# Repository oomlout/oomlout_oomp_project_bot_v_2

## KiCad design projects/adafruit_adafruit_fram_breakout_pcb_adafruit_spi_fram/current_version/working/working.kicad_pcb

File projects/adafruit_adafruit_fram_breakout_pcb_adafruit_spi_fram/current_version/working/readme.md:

# adafruit_fram_breakout_pcb
 
## summary 
* id: adafruit_adafruit_fram_breakout_pcb_adafruit_spi_fram
* user: adafruit
* name: adafruit_fram_breakout_pcb
* board: adafruit_spi_fram
* repo: https://github.com/adafruit/Adafruit-FRAM-Breakout-PCB

* src_file_repo_sch: 
* src_file_repo_sch_link: https://github.com/adafruit/Adafruit-FRAM-Breakout-PCB/tree/master/
* full details link: https://github.com/oomlout/oomlout_oomp_project_bot_v_2/tree/main/projects/adafruit_adafruit_fram_breakout_pcb_adafruit_spi_fram/current_version/working  

## schematic  
  
[schematic (pdf)](working_schematic.pdf) 

## pcb  

[board (pdf)](working.pdf)  

## working_bom
| Id | Designator | Footprint | Quantity | Designation | Supplier and ref |  | None | 
| --- | --- | --- | --- | --- | --- | --- | --- | 
| 1 | FID2,FID1 | FIDUCIAL_1MM | 2 | FIDUCIAL" |  |  | [''] | 
| 2 | U$5,U$6 | MOUNTINGHOLE_2.5_PLATED | 2 | MOUNTINGHOLE2.5 |  |  | [''] | 
| 3 | C1 | _0805MP | 1 | 10uF |  |  | [''] | 
| 4 | JP1 | 1X08_ROUND_70 | 1 |  |  |  | [''] | 
| 5 | R2,R1 | _0805MP | 2 | 10K |  |  | [''] | 
| 6 | U$4 | ADAFRUIT_3.5MM | 1 |  |  |  | [''] | 
| 7 | U1 | SOIC8_208MIL | 1 | MB85RC256VPF-G-JNERE2 |  |  | [''] | 

## bom_schematic
| Ref | Qnty | Value | Cmp name | Footprint | Description | Vendor | DNP | 
| --- | --- | --- | --- | --- | --- | --- | --- | 
| C1 | 1 | 10uF | CAP_CERAMIC_0805MP | working:_0805MP |  |  |  | 
| FID1, FID2 | 2 | FIDUCIAL"" | FIDUCIAL{dblquote}{dblquote} | working:FIDUCIAL_1MM |  |  |  | 
| JP1 | 1 | HEADER-1X870MIL | HEADER-1X870MIL | working:1X08_ROUND_70 |  |  |  | 
| R1, R2 | 2 | 10K | RESISTOR_0805MP | working:_0805MP |  |  |  | 
| U1 | 1 | MB85RC256VPF-G-JNERE2 | FRAM_SOIC8_I2C | working:SOIC8_208MIL |  |  |  | 
| U$5, U$6 | 2 | MOUNTINGHOLE2.5 | MOUNTINGHOLE2.5 | working:MOUNTINGHOLE_2.5_PLATED |  |  |  | 

## mounting_holes
| x | y | package | value | ref | size | 
| --- | --- | --- | --- | --- | --- | 
| 0.0 | 0.0 | MOUNTINGHOLE_2.5_PLATED | MOUNTINGHOLE2.5 | U$5 | m3 | 
| 15.24 | 0.0 | MOUNTINGHOLE_2.5_PLATED | MOUNTINGHOLE2.5 | U$6 | m3 |

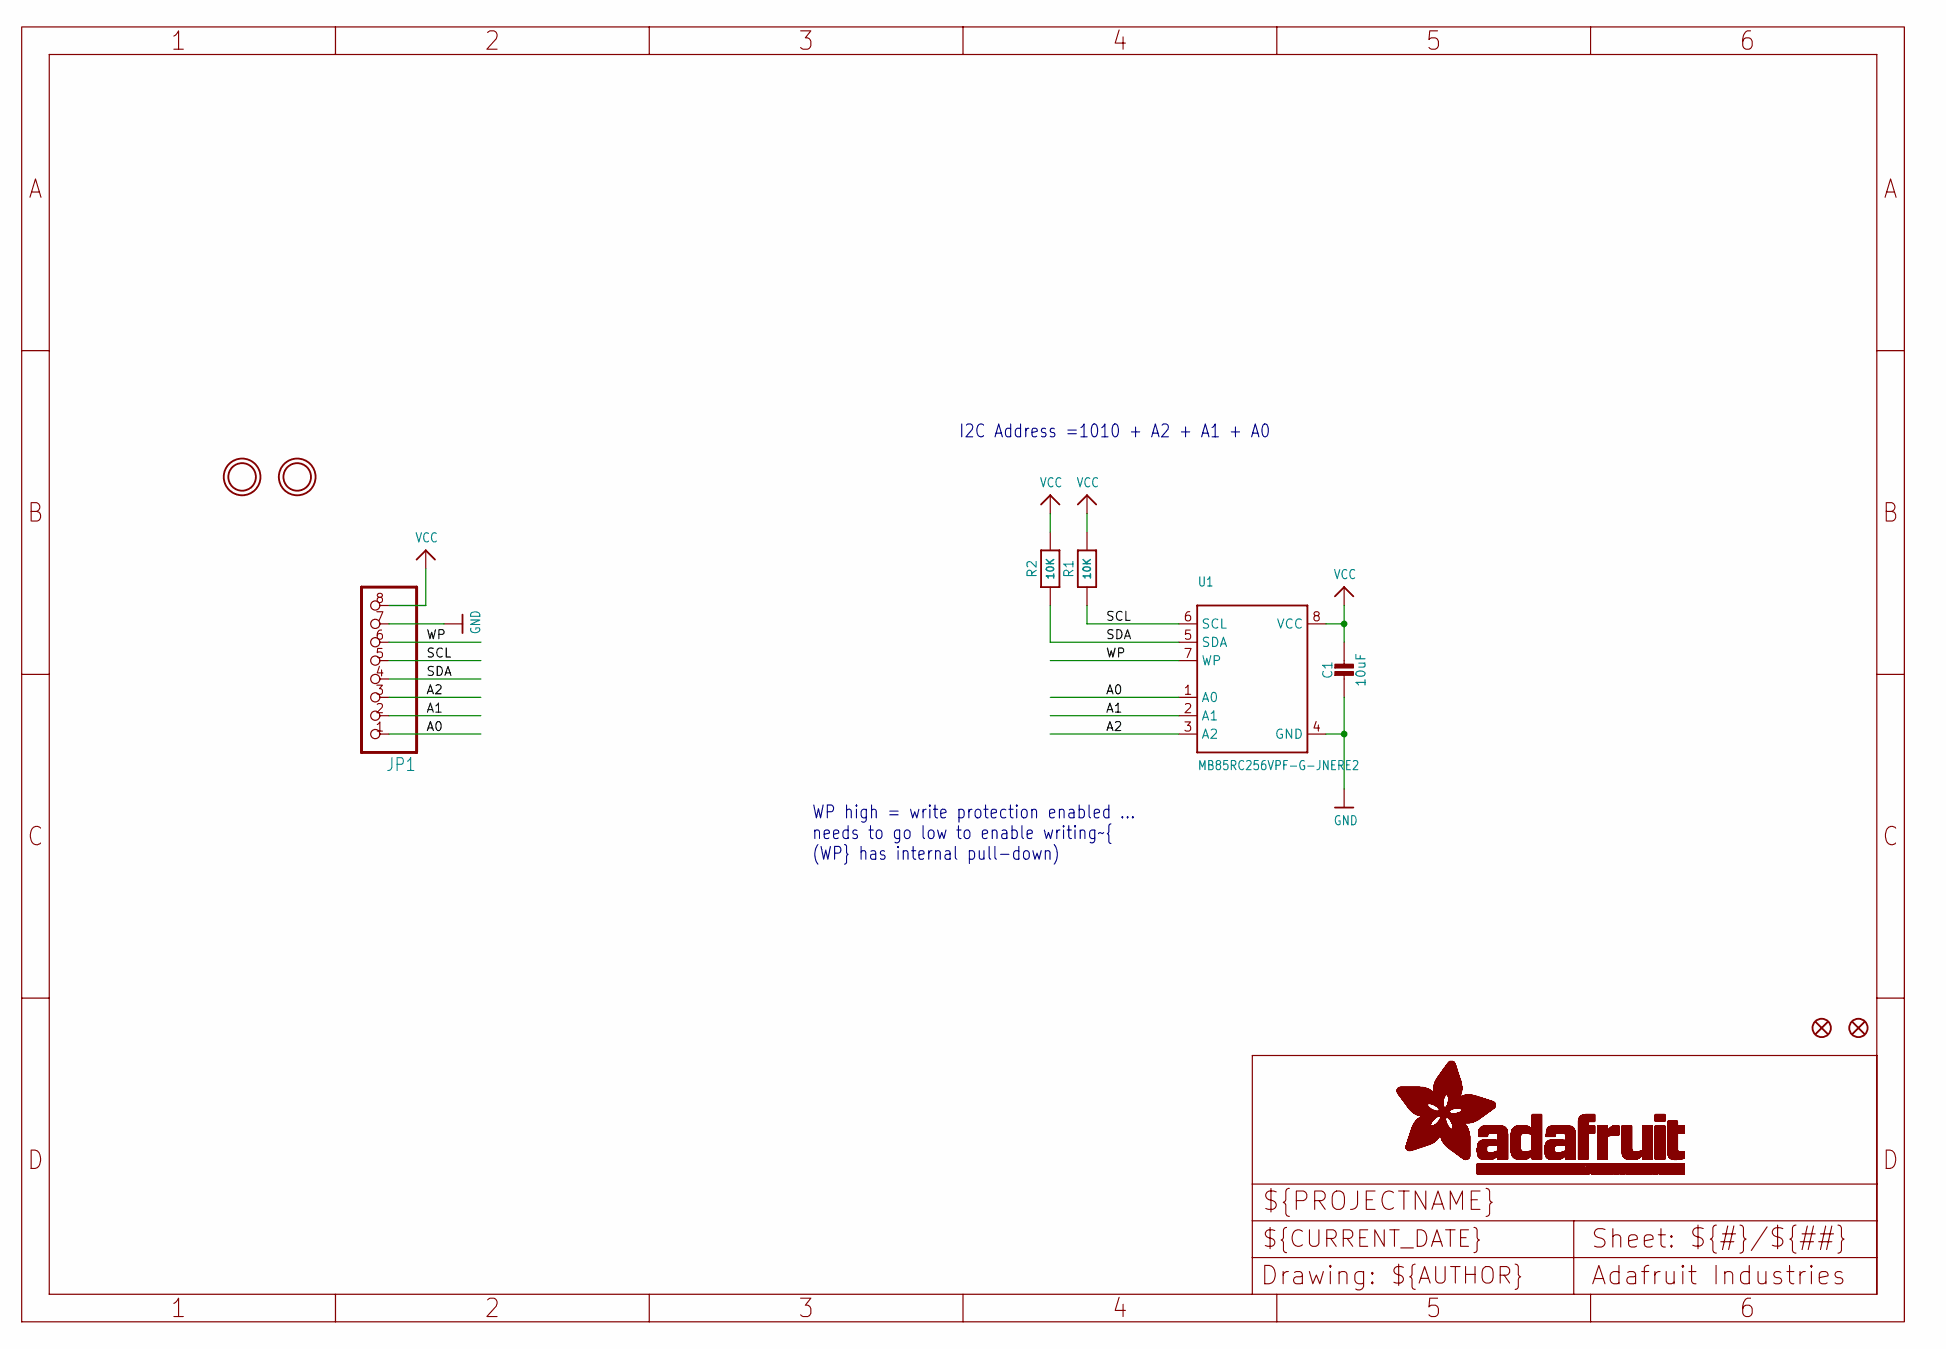
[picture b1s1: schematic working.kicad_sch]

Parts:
C1: 10uF; _0805MP
FID1, FID2: FIDUCIAL""; FIDUCIAL_1MM
JP1: HEADER-1X870MIL; 1X08_ROUND_70
R1, R2: 10K; _0805MP
U1: MB85RC256VPF-G-JNERE2; SOIC8_208MIL
U$5, U$6: MOUNTINGHOLE2.5; MOUNTINGHOLE_2.5_PLATED

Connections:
A0: JP1.1, U1.1 (A0)
A1: JP1.2, U1.2 (A1)
A2: JP1.3, U1.3 (A2)
GND: C1.2, JP1.7, U1.4 (GND)
SCL: JP1.5, R1.1, U1.6 (SCL)
SDA: JP1.4, R2.1, U1.5 (SDA)
VCC: C1.1, JP1.8, R1.2, R2.2, U1.8 (VCC)
WP: JP1.6, U1.7 (WP)

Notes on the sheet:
I2C Address =1010 + A2 + A1 + A0
WP high = write protection enabled ... needs to go low to enable writing~{ (WP} has internal pull-down)

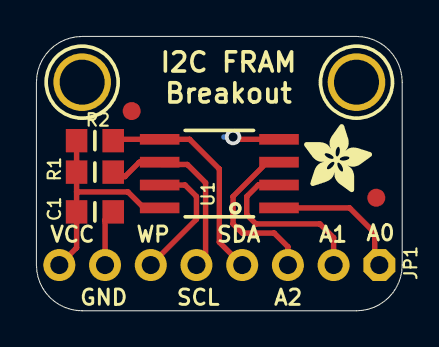
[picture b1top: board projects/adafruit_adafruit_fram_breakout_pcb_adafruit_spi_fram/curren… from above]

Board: 2 copper layers, 20.3 x 15.2 mm, 10 parts (0 on the bottom side), 8 nets.

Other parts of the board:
U$4: ADAFRUIT_3.5MM

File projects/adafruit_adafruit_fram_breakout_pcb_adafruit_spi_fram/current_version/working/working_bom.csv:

"Id";"Designator";"Footprint";"Quantity";"Designation";"Supplier and ref";
1;"FID2,FID1";"FIDUCIAL_1MM";2;"FIDUCIAL""";;;
2;"U$5,U$6";"MOUNTINGHOLE_2.5_PLATED";2;"MOUNTINGHOLE2.5";;;
3;"C1";"_0805MP";1;"10uF";;;
4;"JP1";"1X08_ROUND_70";1;"";;;
5;"R2,R1";"_0805MP";2;"10K";;;
6;"U$4";"ADAFRUIT_3.5MM";1;"";;;
7;"U1";"SOIC8_208MIL";1;"MB85RC256VPF-G-JNERE2";;;

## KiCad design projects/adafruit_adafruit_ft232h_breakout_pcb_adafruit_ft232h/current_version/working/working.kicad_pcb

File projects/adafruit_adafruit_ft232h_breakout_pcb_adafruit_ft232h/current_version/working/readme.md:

# adafruit_ft232h_breakout_pcb
 
## summary 
* id: adafruit_adafruit_ft232h_breakout_pcb_adafruit_ft232h
* user: adafruit
* name: adafruit_ft232h_breakout_pcb
* board: adafruit_ft232h
* repo: https://github.com/adafruit/Adafruit-FT232H-Breakout-PCB

* src_file_repo_sch: 
* src_file_repo_sch_link: https://github.com/adafruit/Adafruit-FT232H-Breakout-PCB/tree/master/
* full details link: https://github.com/oomlout/oomlout_oomp_project_bot_v_2/tree/main/projects/adafruit_adafruit_ft232h_breakout_pcb_adafruit_ft232h/current_version/working  

## schematic  
  
[schematic (pdf)](working_schematic.pdf) 

## pcb  

[board (pdf)](working.pdf)  

## working_bom
| Id | Designator | Footprint | Quantity | Designation | Supplier and ref |  | None | 
| --- | --- | --- | --- | --- | --- | --- | --- | 
| 1 | R2 | 0805-NO | 1 | 12K 1% |  |  | [''] | 
| 2 | R4,R3 | 0805-NO | 2 | 1K |  |  | [''] | 
| 3 | LED1 | CHIPLED_0805_NOOUTLINE | 1 | green |  |  | [''] | 
| 4 | U$8 | ADAFRUIT_5MM | 1 |  |  |  | [''] | 
| 5 | U$11 | PCBFEAT-REV-040 | 1 |  |  |  | [''] | 
| 6 | X1 | 4UCONN_20329 | 1 | MiniB |  |  | [''] | 
| 7 | U$6,U$4,U$7,U$5 | MOUNTINGHOLE_2.5_PLATED | 4 | MOUNTINGHOLE2.5 |  |  | [''] | 
| 8 | IC1 | SOT23-6 | 1 | 93LC56B |  |  | [''] | 
| 9 | C8,C7,C6,C2 | 0805-NO | 4 | 0.1uF |  |  | [''] | 
| 10 | FID1,FID2 | FIDUCIAL_1MM | 2 | FIDUCIAL" |  |  | [''] | 
| 11 | FB2,FB1 | _0805 | 2 | Ferrite |  |  | [''] | 
| 12 | R5 | _0805MP | 1 | 2.2K |  |  | [''] | 
| 13 | C4,C1,C3,C5 | 0805-NO | 4 | 10uF |  |  | [''] | 
| 14 | R6 | 0805-NO | 1 | 4.7K |  |  | [''] | 
| 15 | IC2 | QFN48_8MM | 1 | FT232HQ |  |  | [''] | 
| 16 | LED2 | CHIPLED_0805_NOOUTLINE | 1 | red |  |  | [''] | 
| 17 | R7,R1 | 0805-NO | 2 | 12K |  |  | [''] | 
| 18 | U$2,U$3 | 1X10-BIG | 2 | PINHD-1X10 |  |  | [''] | 
| 19 | Q1 | RESONATOR-SMD | 1 | CSTCR 12MHz |  |  | [''] | 
| 20 | U$9 | ADAFRUIT_TEXT_30MM | 1 |  |  |  | [''] | 

## bom_schematic
| Ref | Qnty | Value | Cmp name | Footprint | Description | Vendor | DNP | 
| --- | --- | --- | --- | --- | --- | --- | --- | 
| C1, C3, C4, C5 | 4 | 10uF | CAP_CERAMIC0805-NOOUTLINE | working:0805-NO |  |  |  | 
| C2, C6, C7, C8 | 4 | 0.1uF | CAP_CERAMIC0805-NOOUTLINE | working:0805-NO |  |  |  | 
| FB1, FB2 | 2 | Ferrite | FERRITE_0805 | working:_0805 |  |  |  | 
| FID1, FID2 | 2 | FIDUCIAL"" | FIDUCIAL{dblquote}{dblquote} | working:FIDUCIAL_1MM |  |  |  | 
| IC1 | 1 | 9376?A | 9376?A | working:SOT23-6 |  |  |  | 
| IC2 | 1 | FT232HQ | FT232HQ | working:QFN48_8MM |  |  |  | 
| LED1 | 1 | green | LED0805_NOOUTLINE | working:CHIPLED_0805_NOOUTLINE |  |  |  | 
| LED2 | 1 | red | LED0805_NOOUTLINE | working:CHIPLED_0805_NOOUTLINE |  |  |  | 
| Q1 | 1 | RESONATORSMD | RESONATORSMD | working:RESONATOR-SMD |  |  |  | 
| R1, R7 | 2 | 12K | RESISTOR0805_NOOUTLINE | working:0805-NO |  |  |  | 
| R2 | 1 | 12K 1% | RESISTOR0805_NOOUTLINE | working:0805-NO |  |  |  | 
| R3, R4 | 2 | 1K | RESISTOR0805_NOOUTLINE | working:0805-NO |  |  |  | 
| R5 | 1 | 2.2K | RESISTOR_0805MP | working:_0805MP |  |  |  | 
| R6 | 1 | 4.7K | RESISTOR0805_NOOUTLINE | working:0805-NO |  |  |  | 
| U$2, U$3 | 2 | PINHD-1X10 | PINHD-1X10 | working:1X10-BIG |  |  |  | 
| U$4, U$5, U$6, U$7 | 4 | MOUNTINGHOLE2.5 | MOUNTINGHOLE2.5 | working:MOUNTINGHOLE_2.5_PLATED |  |  |  | 
| X1 | 1 | MiniB | USBMICRO_20329 | working:4UCONN_20329 |  |  |  | 

## mounting_holes
| x | y | package | value | ref | size | 
| --- | --- | --- | --- | --- | --- | 
| 0.0 | 17.78 | MOUNTINGHOLE_2.5_PLATED | MOUNTINGHOLE2.5 | U$4 | m3 | 
| 0.0 | 0.0 | MOUNTINGHOLE_2.5_PLATED | MOUNTINGHOLE2.5 | U$5 | m3 | 
| 33.02 | 17.78 | MOUNTINGHOLE_2.5_PLATED | MOUNTINGHOLE2.5 | U$6 | m3 | 
| 33.02 | 0.0 | MOUNTINGHOLE_2.5_PLATED | MOUNTINGHOLE2.5 | U$7 | m3 |

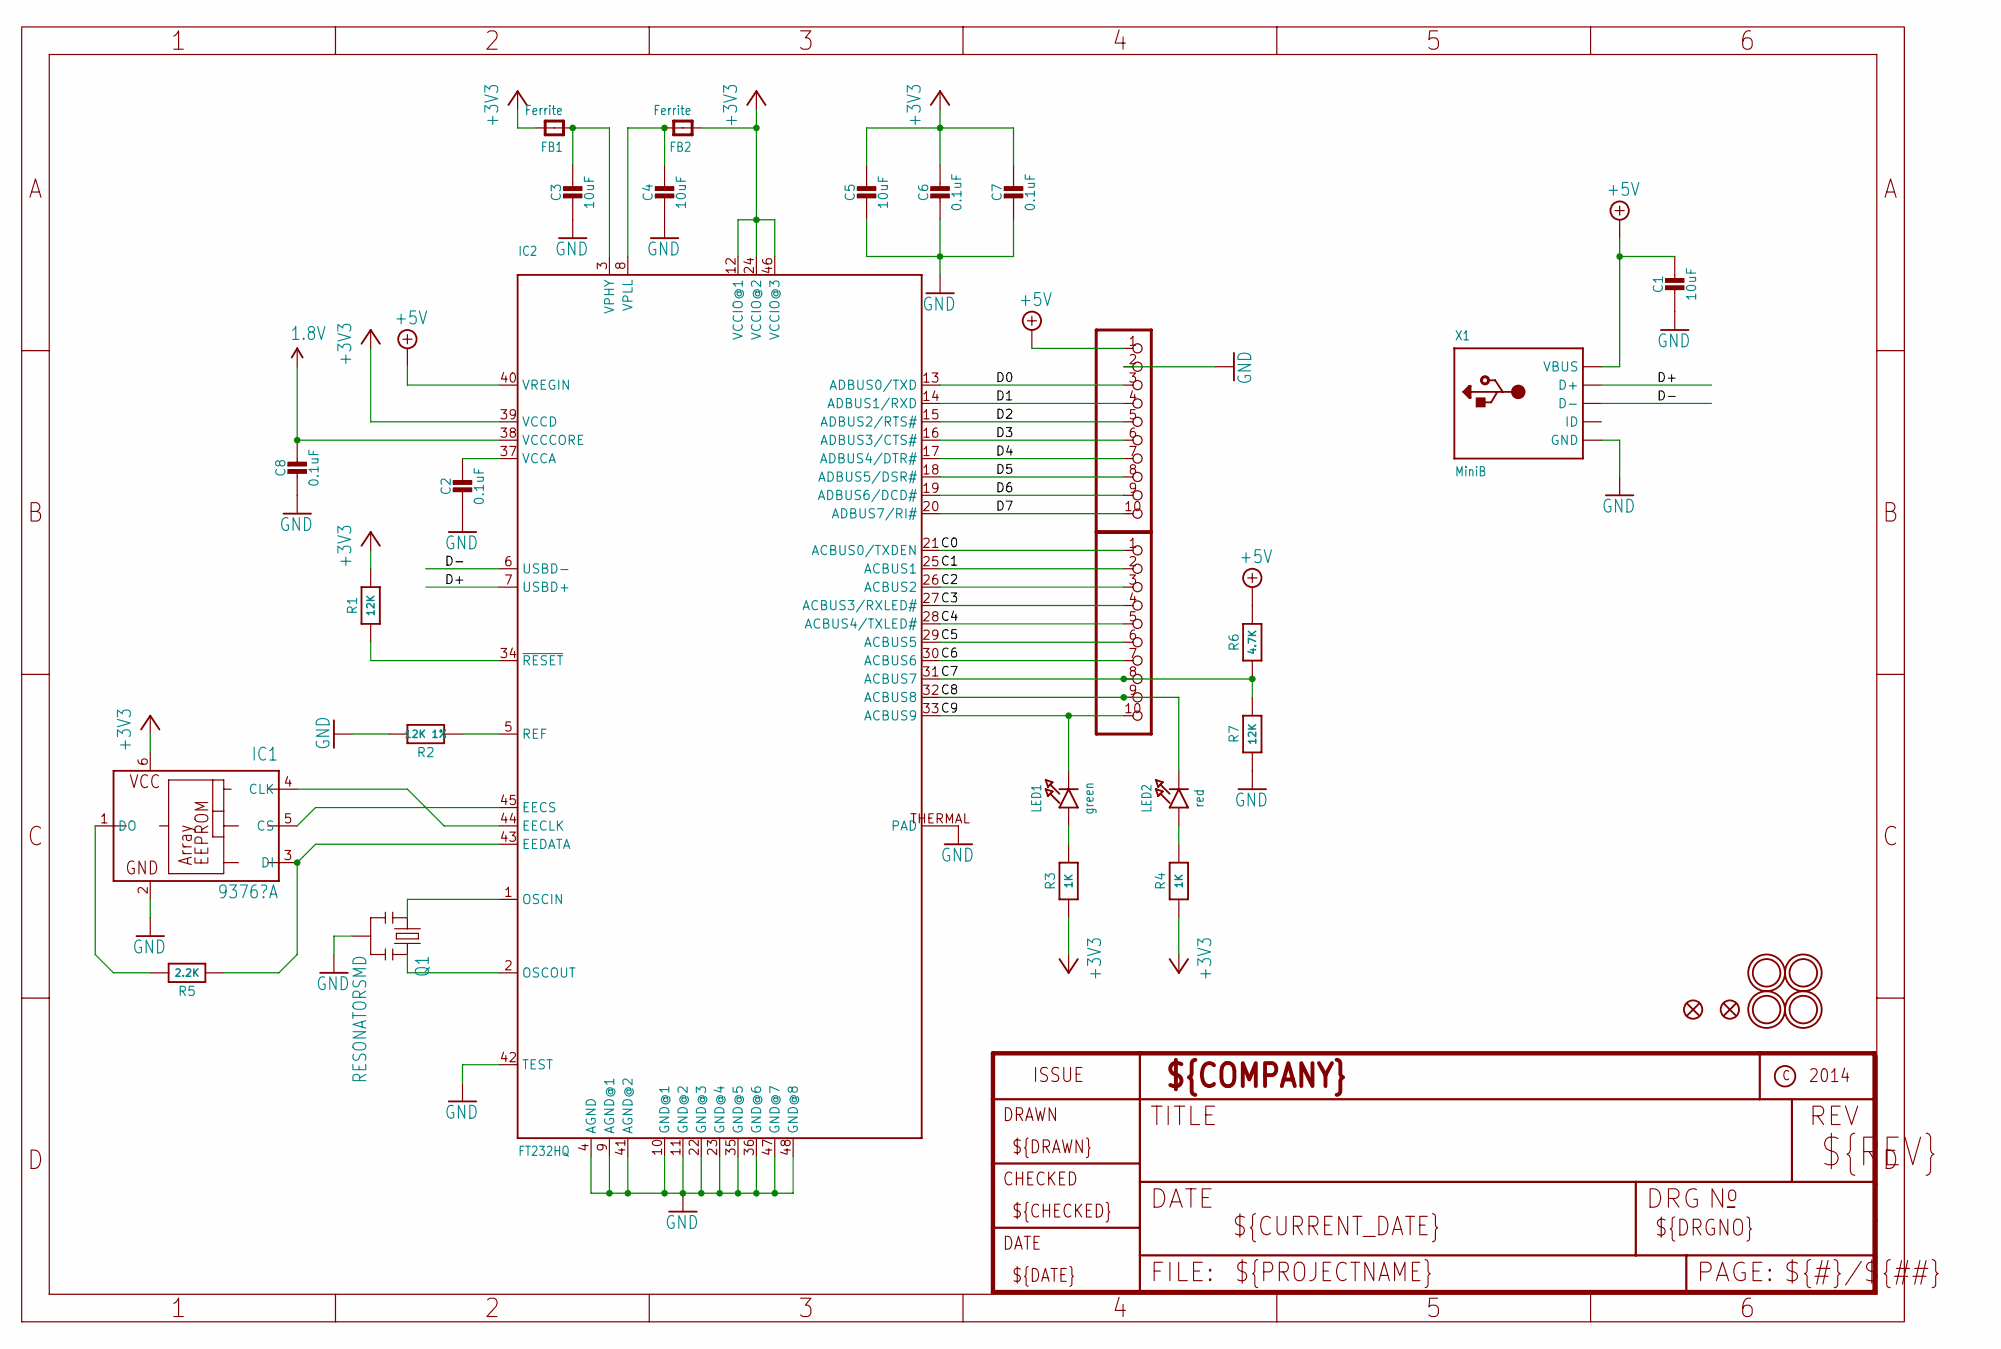
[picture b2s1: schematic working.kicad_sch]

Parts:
C1, C3, C4, C5: 10uF; 0805-NO
C2, C6, C7, C8: 0.1uF; 0805-NO
FB1, FB2: Ferrite; _0805
FID1, FID2: FIDUCIAL""; FIDUCIAL_1MM
IC1: 9376?A; SOT23-6
IC2: FT232HQ; QFN48_8MM
LED1: green; CHIPLED_0805_NOOUTLINE
LED2: red; CHIPLED_0805_NOOUTLINE
Q1: RESONATORSMD; RESONATOR-SMD
R1, R7: 12K; 0805-NO
R2: 12K 1%; 0805-NO
R3, R4: 1K; 0805-NO
R5: 2.2K; _0805MP
R6: 4.7K; 0805-NO
U$2, U$3: PINHD-1X10; 1X10-BIG
U$4, U$5, U$6, U$7: MOUNTINGHOLE2.5; MOUNTINGHOLE_2.5_PLATED
X1: MiniB; 4UCONN_20329

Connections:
1.8V: C8.1, IC2.38 (VCCCORE)
+3V3: C5.1, C6.1, C7.1, FB1.2, FB2.1, IC1.6 (VCC), IC2.12 (VCCIO@1), IC2.24 (VCCIO@2), IC2.39 (VCCD), IC2.46 (VCCIO@3), R1.2, R3.1, R4.1
+5V: C1.1, IC2.40 (VREGIN), R6.2, U$2.1, X1.VBUS
C0: IC2.21 (ACBUS0/TXDEN), U$3.1
C1: IC2.25 (ACBUS1), U$3.2
C2: IC2.26 (ACBUS2), U$3.3
C3: IC2.27 (ACBUS3/RXLED#), U$3.4
C4: IC2.28 (ACBUS4/TXLED#), U$3.5
C5: IC2.29 (ACBUS5), U$3.6
C6: IC2.30 (ACBUS6), U$3.7
C7: IC2.31 (ACBUS7), R6.1, R7.2, U$3.8
C8: IC2.32 (ACBUS8), LED2.C, U$3.9
C9: IC2.33 (ACBUS9), LED1.C, U$3.10
D0: IC2.13 (ADBUS0/TXD), U$2.3
D1: IC2.14 (ADBUS1/RXD), U$2.4
D2: IC2.15 (ADBUS2/RTS#), U$2.5
D3: IC2.16 (ADBUS3/CTS#), U$2.6
D4: IC2.17 (ADBUS4/DTR#), U$2.7
D5: IC2.18 (ADBUS5/DSR#), U$2.8
D6: IC2.19 (ADBUS6/DCD#), U$2.9
D7: IC2.20 (ADBUS7/RI#), U$2.10
D+: IC2.7 (USBD+), X1.D+
D-: IC2.6 (USBD-), X1.D-
GND: C1.2, C2.2, C3.2, C4.2, C5.2, C6.2, C7.2, C8.2, IC1.2 (GND), IC2.4 (AGND), IC2.9 (AGND@1), IC2.10 (GND@1), IC2.11 (GND@2), IC2.22 (GND@3), IC2.23 (GND@4), IC2.35 (GND@5), IC2.36 (GND@6), IC2.41 (AGND@2), IC2.42 (TEST), IC2.47 (GND@7), IC2.48 (GND@8), IC2.THERMAL (PAD), Q1.2, R2.2, R7.1, U$2.2, X1.BASE@1 (GND), X1.BASE@2 (GND), X1.GND, X1.SPRT@1 (GND), X1.SPRT@2 (GND), X1.SPRT@3 (GND), X1.SPRT@4 (GND)
unnamed: IC2.1 (OSCIN), Q1.1
unnamed: IC2.2 (OSCOUT), Q1.3
unnamed: IC2.5 (REF), R2.1
unnamed: LED2.A, R4.2
unnamed: IC2.34 (~RESET), R1.1
unnamed: LED1.A, R3.2
unnamed: IC1.3 (DI), IC2.43 (EEDATA), R5.1
unnamed: IC1.5 (CS), IC2.45 (EECS)
unnamed: IC1.4 (CLK), IC2.44 (EECLK)
unnamed: IC1.1 (DO), R5.2
VCCA: C2.1, IC2.37 (VCCA)
VPHY: C3.1, FB1.1, IC2.3 (VPHY)
VPLL: C4.1, FB2.2, IC2.8 (VPLL)

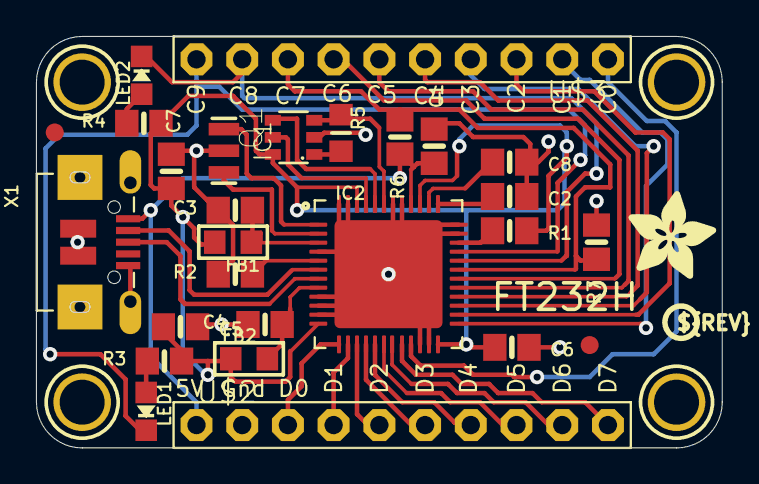
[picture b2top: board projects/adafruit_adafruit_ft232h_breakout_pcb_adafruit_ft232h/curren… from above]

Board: 2 copper layers, 38.1 x 22.9 mm, 34 parts (1 on the bottom side), 37 nets.

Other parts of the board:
U$8: ADAFRUIT_5MM
U$9: ADAFRUIT_TEXT_30MM
U$11: PCBFEAT-REV-040

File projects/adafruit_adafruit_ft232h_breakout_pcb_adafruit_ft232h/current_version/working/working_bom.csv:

"Id";"Designator";"Footprint";"Quantity";"Designation";"Supplier and ref";
1;"R2";"0805-NO";1;"12K 1%";;;
2;"R4,R3";"0805-NO";2;"1K";;;
3;"LED1";"CHIPLED_0805_NOOUTLINE";1;"green";;;
4;"U$8";"ADAFRUIT_5MM";1;"";;;
5;"U$11";"PCBFEAT-REV-040";1;"";;;
6;"X1";"4UCONN_20329";1;"MiniB";;;
7;"U$6,U$4,U$7,U$5";"MOUNTINGHOLE_2.5_PLATED";4;"MOUNTINGHOLE2.5";;;
8;"IC1";"SOT23-6";1;"93LC56B";;;
9;"C8,C7,C6,C2";"0805-NO";4;"0.1uF";;;
10;"FID1,FID2";"FIDUCIAL_1MM";2;"FIDUCIAL""";;;
11;"FB2,FB1";"_0805";2;"Ferrite";;;
12;"R5";"_0805MP";1;"2.2K";;;
13;"C4,C1,C3,C5";"0805-NO";4;"10uF";;;
14;"R6";"0805-NO";1;"4.7K";;;
15;"IC2";"QFN48_8MM";1;"FT232HQ";;;
16;"LED2";"CHIPLED_0805_NOOUTLINE";1;"red";;;
17;"R7,R1";"0805-NO";2;"12K";;;
18;"U$2,U$3";"1X10-BIG";2;"PINHD-1X10";;;
19;"Q1";"RESONATOR-SMD";1;"CSTCR 12MHz";;;
20;"U$9";"ADAFRUIT_TEXT_30MM";1;"";;;

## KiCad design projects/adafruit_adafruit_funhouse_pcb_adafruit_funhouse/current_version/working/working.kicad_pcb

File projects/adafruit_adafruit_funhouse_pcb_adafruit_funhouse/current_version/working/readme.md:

# adafruit_funhouse_pcb
 
## summary 
* id: adafruit_adafruit_funhouse_pcb_adafruit_funhouse
* user: adafruit
* name: adafruit_funhouse_pcb
* board: adafruit_funhouse
* repo: https://github.com/adafruit/Adafruit-FunHouse-PCB

* src_file_repo_sch: 
* src_file_repo_sch_link: https://github.com/adafruit/Adafruit-FunHouse-PCB/tree/main/
* full details link: https://github.com/oomlout/oomlout_oomp_project_bot_v_2/tree/main/projects/adafruit_adafruit_funhouse_pcb_adafruit_funhouse/current_version/working  

## schematic  
  
[schematic (pdf)](working_schematic.pdf) 

## pcb  

[board (pdf)](working.pdf)  

## working_bom
| Id | Designator | Footprint | Quantity | Designation | Supplier and ref |  | None | 
| --- | --- | --- | --- | --- | --- | --- | --- | 
| 1 | R9,R20,R5,R1,R13,R10,R7,R4,R12 | 0603-NO | 9 | 10K |  |  | [''] | 
| 2 | X1 | CAPTOUCH_6X9MM | 1 | CAPTOUCH_10MM |  |  | [''] | 
| 3 | U5 | SNR6-1.0-3X3X1MM | 1 | AHT20 |  |  | [''] | 
| 4 | X6 | CAPTOUCH_5SLIDER | 1 | CAPTOUCH_5SLIDER_10MM |  |  | [''] | 
| 5 | SW5,SW2,SW6,SW7 | TACTILE_3X6MM | 4 | FSM2JMTR |  |  | [''] | 
| 6 | TFT1 | TFT_1.54IN_240X240_22PIN | 1 | DISP_TFT_1.54IN_240X240_22P |  |  | [''] | 
| 7 | U$45 | FUNHOUSE_FRONT | 1 |  |  |  | [''] | 
| 8 | ON0 | CHIPLED_0603_NOOUTLINE | 1 | GREEN |  |  | [''] | 
| 9 | DS4,DS1,DS3,DS2,DS0 | APA102_2020 | 5 | APA102-2020 |  |  | [''] | 
| 10 | FID2,FID1,FID3,FID4,FID5,FID6 | FIDUCIAL_1MM | 6 | FIDUCIAL_1MM |  |  | [''] | 
| 11 | U1 | BMX280_COMBO | 1 | DPS3 |  |  | [''] | 
| 12 | U2 | ALS-PT19-315C | 1 | ALS-PT19 |  |  | [''] | 
| 13 | L0 | CHIPLED_0603_NOOUTLINE | 1 | RED |  |  | [''] | 
| 14 | X3,X5 | CAPTOUCH_7X9MM | 2 | CAPTOUCH_10MM |  |  | [''] | 
| 15 | SP1 | BUZZER_SMT_7.5MM | 1 | 7.5mm SPK |  |  | [''] | 
| 16 | R6 | 0603-NO | 1 | 47K |  |  | [''] | 
| 17 | SW3 | EG1390 | 1 | EG1390 |  |  | [''] | 
| 18 | C12,C14,C6 | 0603-NO | 3 | 1uF |  |  | [''] | 
| 19 | C3,C10,C7,C4,C13,C11,C17 | 0805-NO | 7 | 10ÂµF |  |  | [''] | 
| 20 | TP8,TP7,TP5,TP4 | SMT_NUT_3MM | 4 | SEWTAP_SMTNUTM3 |  |  | [''] | 
| 21 | SW4 | KMR2 | 1 | SPST_TACT-KMR2 |  |  | [''] | 
| 22 | D6,D1,D2 | SOD-323 | 3 | 3.6V |  |  | [''] | 
| 23 | R18,R16,R2 | 0603-NO | 3 | 1K |  |  | [''] | 
| 24 | Q3 | SOT23-R | 1 | DMG3415U-7 |  |  | [''] | 
| 25 | SJ2 | SOLDERJUMPER_2WAY_OPEN_NOPASTE | 1 |  |  |  | [''] | 
| 26 | TP2,TP6,TP3,TP1 | TESTPOINT_ROUND_1.5MM_NO | 4 |  |  |  | [''] | 
| 27 | CONN1 | JST_SH4 | 1 | STEMMA_I2C_QT |  |  | [''] | 
| 28 | C2,C15,C5 | 0603-NO | 3 | 0.1uF |  |  | [''] | 
| 29 | C20,C1 | 0805-NO | 2 | 10uF |  |  | [''] | 
| 30 | Q1 | SOT23-WIDE | 1 | BSS138 |  |  | [''] | 
| 31 | SENSE1,SENSE3,SENSE0 | JSTPH3 | 3 | JST PH 3 |  |  | [''] | 
| 32 | R11 | 0603-NO | 1 | 100 |  |  | [''] | 
| 33 | SJ1 | SOLDERJUMPER_CLOSEDWIRE | 1 |  |  |  | [''] | 
| 34 | C9 | 0805_10MGAP | 1 | 10uF/10V+ |  |  | [''] | 
| 35 | R14,R17 | 0603-NO | 2 | 1Meg |  |  | [''] | 
| 36 | R3,R8 | 0603-NO | 2 | 5.1K |  |  | [''] | 
| 37 | X4 | USB_C_CUSB31-CFM2AX-01-X | 1 | USB C |  |  | [''] | 
| 38 | U$41 | PCBFEAT-REV-040 | 1 |  |  |  | [''] | 
| 39 | JP2 | 2X03_SMTTHM | 1 |  |  |  | [''] | 
| 40 | U4 | SOT23-5 | 1 | AP2112K-3.3 |  |  | [''] | 
| 41 | D3 | SOD-323F | 1 | 1N4148 |  |  | [''] | 
| 42 | Q4 | SOT23-R | 1 | BSS138 |  |  | [''] | 
| 43 | JP1 | 2X03_SMT_4UCON_14113 | 1 | 2x3 SMT |  |  | [''] | 
| 44 | U3 | MODULE_ESP32-S2-WROVER | 1 | ESP32-S2-MODULE_WROVER |  |  | [''] | 
| 45 | U$69 | FUNHOUSE_BACK | 1 |  |  |  | [''] | 

## bom_schematic
| Ref | Qnty | Value | Cmp name | Footprint | Description | Vendor | DNP | 
| --- | --- | --- | --- | --- | --- | --- | --- | 
| C1, C20 | 2 | 10uF | CAP_CERAMIC0805-NOOUTLINE | working:0805-NO |  |  |  | 
| C2, C5, C15 | 3 | 0.1uF | CAP_CERAMIC0603_NO | working:0603-NO |  |  |  | 
| C3, C4, C7, C10, C11, C13, C17 | 7 | 10ÂµF | CAP_CERAMIC0805-NOOUTLINE | working:0805-NO |  |  |  | 
| C6, C12, C14 | 3 | 1uF | CAP_CERAMIC0603_NO | working:0603-NO |  |  |  | 
| C9 | 1 | 10uF/10V+ | CAP_CERAMIC0805_10MGAP | working:0805_10MGAP |  |  |  | 
| CONN1 | 1 | STEMMA_I2C_QT | STEMMA_I2C_QT | working:JST_SH4 |  |  |  | 
| D1, D2, D6 | 3 | 3.6V | DIODE-ZENERSOD323 | working:SOD-323 |  |  |  | 
| D3 | 1 | 1N4148 | DIODESOD-323F | working:SOD-323F |  |  |  | 
| DS0, DS1, DS2, DS3, DS4 | 5 | APA102-2020 | APA1022020 | working:APA102_2020 |  |  |  | 
| FID1, FID2, FID3, FID4, FID5, FID6 | 6 | FIDUCIAL_1MM | FIDUCIAL_1MM | working:FIDUCIAL_1MM |  |  |  | 
| JP1 | 1 | 2x3 SMT | HEADER-2X314113 | working:2X03_SMT_4UCON_14113 |  |  |  | 
| JP2 | 1 | HEADER-2X3_SMTTHM | HEADER-2X3_SMTTHM | working:2X03_SMTTHM |  |  |  | 
| L0 | 1 | RED | LED0603_NOOUTLINE | working:CHIPLED_0603_NOOUTLINE |  |  |  | 
| ON0 | 1 | GREEN | LED0603_NOOUTLINE | working:CHIPLED_0603_NOOUTLINE |  |  |  | 
| Q1 | 1 | BSS138 | MOSFET-NWIDE | working:SOT23-WIDE |  |  |  | 
| Q3 | 1 | DMG3415U-7 | MOSFET-P | working:SOT23-R |  |  |  | 
| Q4 | 1 | BSS138 | MOSFET-NREFLOW | working:SOT23-R |  |  |  | 
| R1, R4, R5, R7, R9, R10, R12, R13, R20 | 9 | 10K | RESISTOR_0603_NOOUT | working:0603-NO |  |  |  | 
| R2, R16, R18 | 3 | 1K | RESISTOR_0603_NOOUT | working:0603-NO |  |  |  | 
| R3, R8 | 2 | 5.1K | RESISTOR_0603_NOOUT | working:0603-NO |  |  |  | 
| R6 | 1 | 47K | RESISTOR_0603_NOOUT | working:0603-NO |  |  |  | 
| R11 | 1 | 100 | RESISTOR_0603_NOOUT | working:0603-NO |  |  |  | 
| R14, R17 | 2 | 1Meg | RESISTOR_0603_NOOUT | working:0603-NO |  |  |  | 
| SENSE0, SENSE1, SENSE3 | 3 | JST PH 3 | CON_JST_PH_3PIN | working:JSTPH3 |  |  |  | 
| SJ1 | 1 | SOLDERJUMPERCLOSED | SOLDERJUMPERCLOSED | working:SOLDERJUMPER_CLOSEDWIRE |  |  |  | 
| SJ2 | 1 | SOLDERJUMPER_2WAY | SOLDERJUMPER_2WAY | working:SOLDERJUMPER_2WAY_OPEN_NOPASTE |  |  |  | 
| SP1 | 1 | SPEAKER_7.5MM | SPEAKER_7.5MM | working:BUZZER_SMT_7.5MM |  |  |  | 
| SW2, SW5, SW6, SW7 | 4 | FSM2JMTR | SWITCH_PUSHBUTTON_3.5X6MM | working:TACTILE_3X6MM |  |  |  | 
| SW3 | 1 | EG1390 | SWITCH_DPDTEG1390 | working:EG1390 |  |  |  | 
| SW4 | 1 | SPST_TACT-KMR2 | SPST_TACT-KMR2 | working:KMR2 |  |  |  | 
| TFT1 | 1 | DISP_TFT_1.54IN_240X240_22P | DISP_TFT_1.54IN_240X240_22P | working:TFT_1.54IN_240X240_22PIN |  |  |  | 
| TP1, TP2, TP3, TP6 | 4 | TESTPOINTROUND1.5MMNO | TESTPOINTROUND1.5MMNO | working:TESTPOINT_ROUND_1.5MM_NO |  |  |  | 
| TP4, TP5, TP7, TP8 | 4 | SEWTAP_SMTNUTM3 | SEWTAP_SMTNUTM3 | working:SMT_NUT_3MM |  |  |  | 
| U1 | 1 | DPS3 | BMP280_COMBO | working:BMX280_COMBO |  |  |  | 
| U2 | 1 | ALS-PT19 | PHOTOTRANSISTOR_PT19-315C | working:ALS-PT19-315C |  |  |  | 
| U3 | 1 | ESP32-S2-MODULE_WROVER | ESP32-S2-MODULE_WROVER | working:MODULE_ESP32-S2-WROVER |  |  |  | 
| U4 | 1 | AP2112K-3.3 | VREG_SOT23-5 | working:SOT23-5 |  |  |  | 
| U5 | 1 | AHT20 | SENSOR-AHT20 | working:SNR6-1.0-3X3X1MM |  |  |  | 
| X1 | 1 | CAPTOUCH_MONOPAD_6X9 | CAPTOUCH_MONOPAD_6X9 | working:CAPTOUCH_6X9MM |  |  |  | 
| X3, X5 | 2 | CAPTOUCH_MONOPAD_7X9 | CAPTOUCH_MONOPAD_7X9 | working:CAPTOUCH_7X9MM |  |  |  | 
| X4 | 1 | USB C | USB_C | working:USB_C_CUSB31-CFM2AX-01-X |  |  |  | 
| X6 | 1 | CAPTOUCH_5SLIDER_10MM | CAPTOUCH_5SLIDER_10MM | working:CAPTOUCH_5SLIDER |  |  |  |

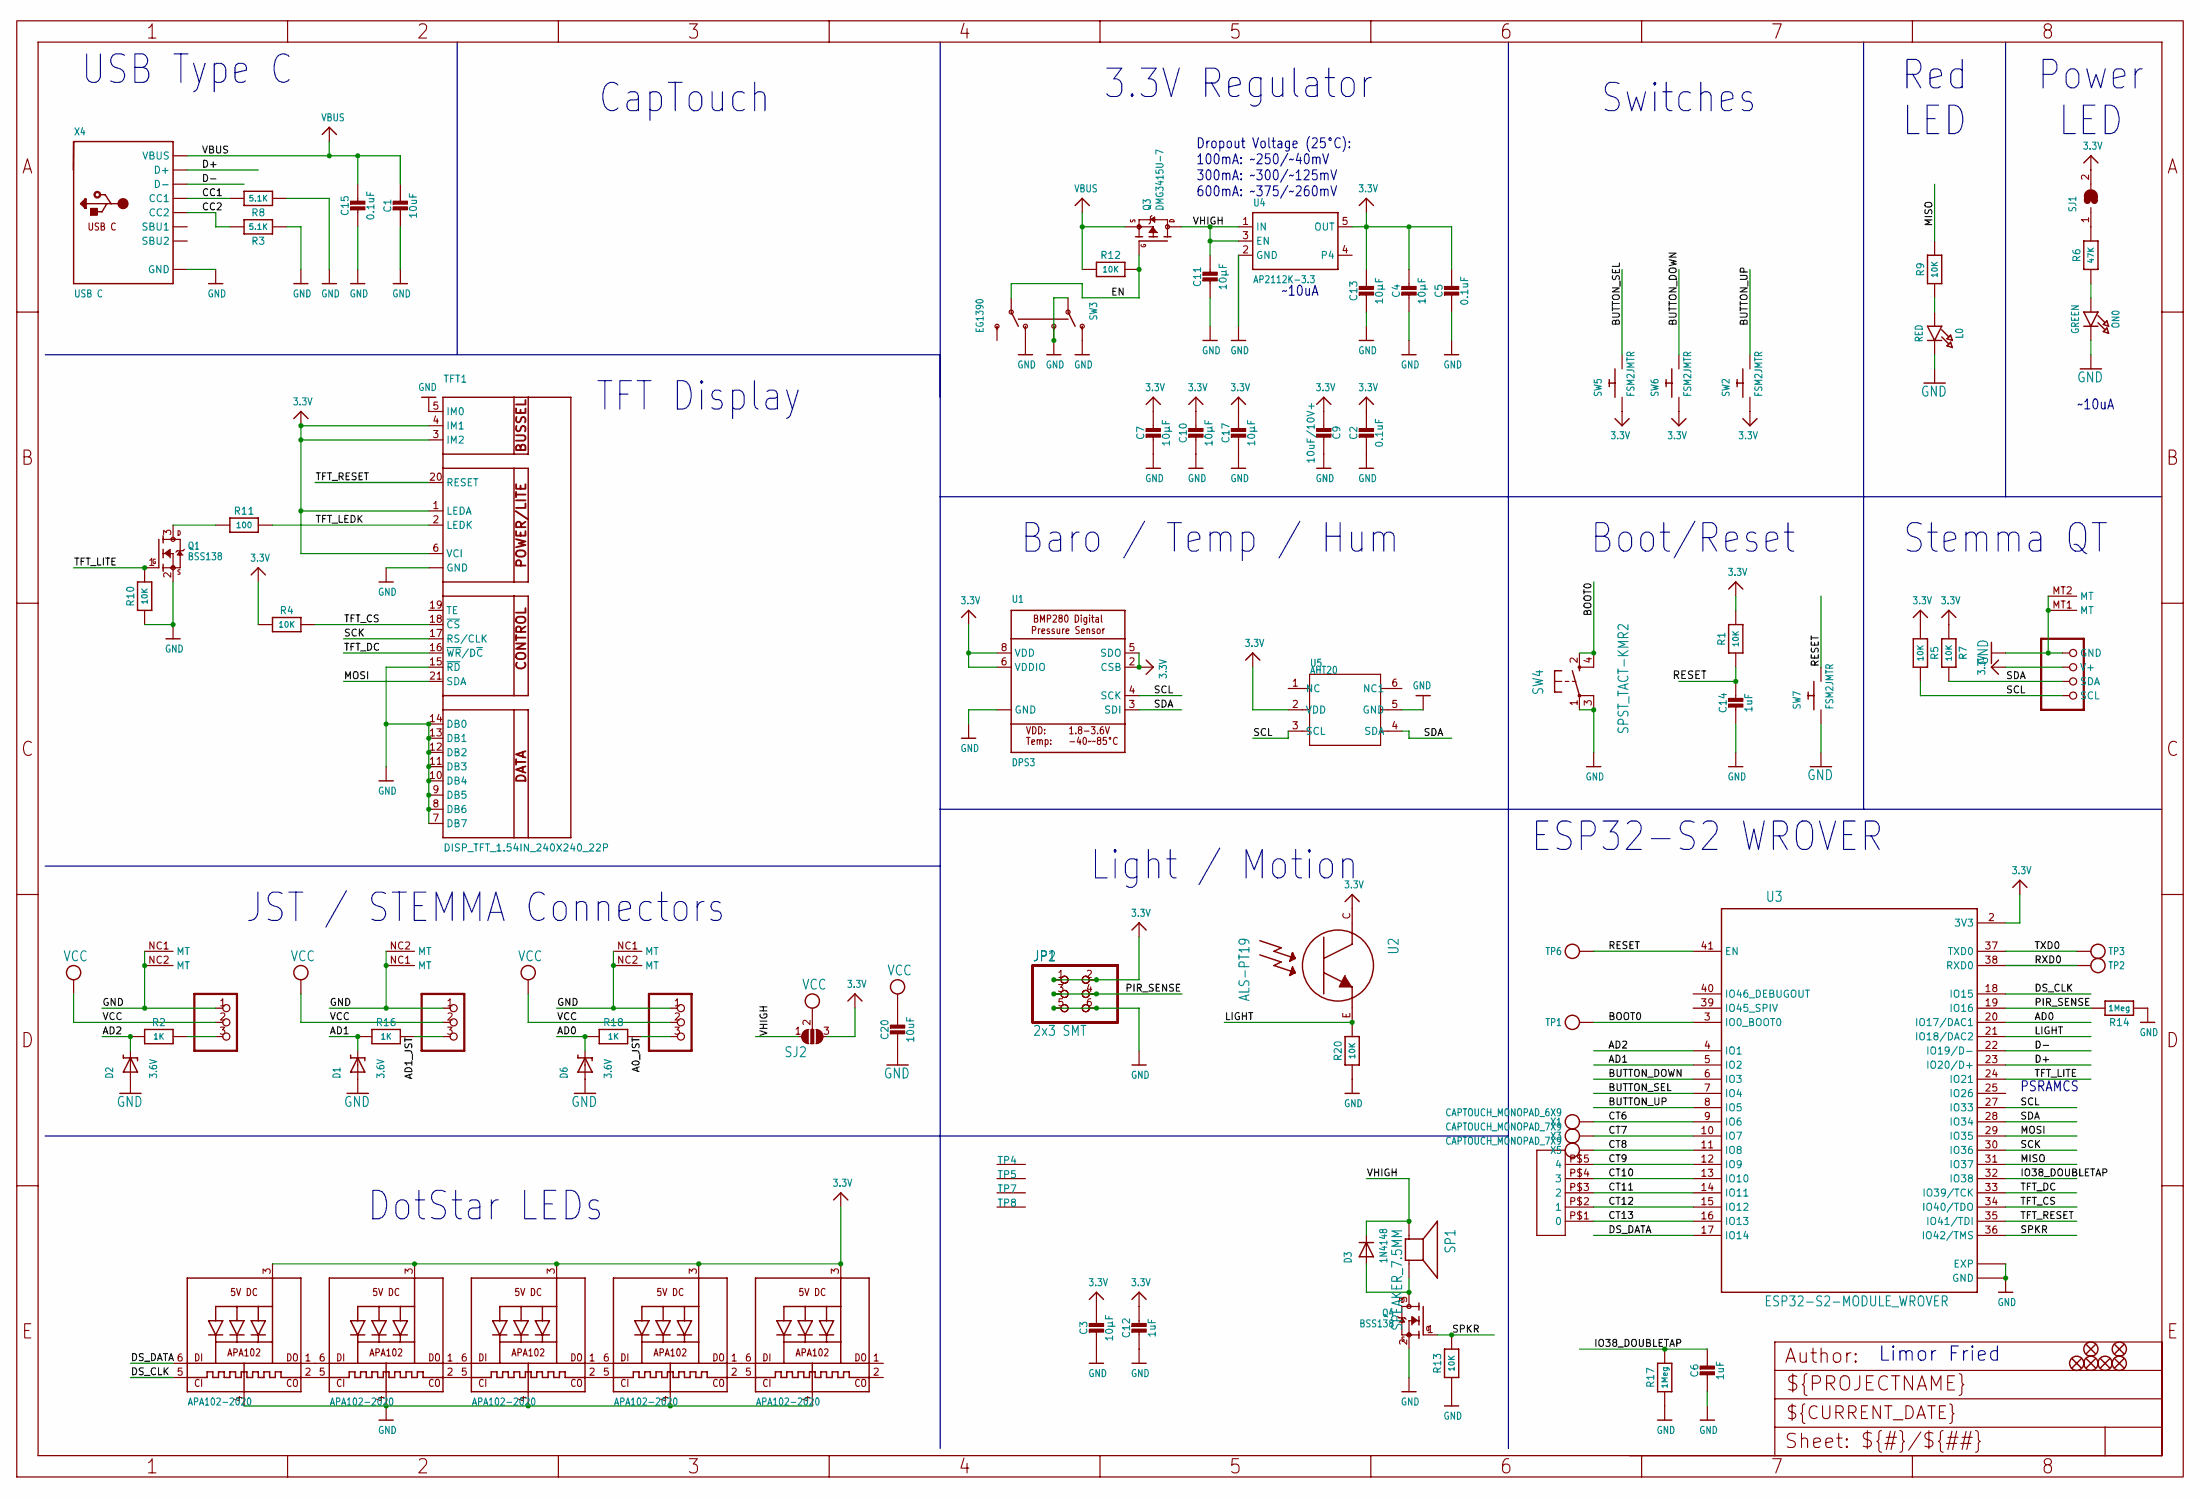
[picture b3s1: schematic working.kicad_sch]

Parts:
C1, C20: 10uF; 0805-NO
C2, C5, C15: 0.1uF; 0603-NO
C3, C4, C7, C10, C11, C13, C17: 10µF; 0805-NO
C6, C12, C14: 1uF; 0603-NO
C9: 10uF/10V+; 0805_10MGAP
CONN1: STEMMA_I2C_QT; JST_SH4
D1, D2, D6: 3.6V; SOD-323
D3: 1N4148; SOD-323F
DS0, DS1, DS2, DS3, DS4: APA102-2020; APA102_2020
FID1, FID2, FID3, FID4, FID5, FID6: FIDUCIAL_1MM
JP1: 2x3 SMT; 2X03_SMT_4UCON_14113
JP2: HEADER-2X3_SMTTHM; 2X03_SMTTHM
L0: RED; CHIPLED_0603_NOOUTLINE
ON0: GREEN; CHIPLED_0603_NOOUTLINE
Q1: BSS138; SOT23-WIDE
Q3: DMG3415U-7; SOT23-R
Q4: BSS138; SOT23-R
R1, R4, R5, R7, R9, R10, R12, R13, R20: 10K; 0603-NO
R2, R16, R18: 1K; 0603-NO
R3, R8: 5.1K; 0603-NO
R6: 47K; 0603-NO
R11: 100; 0603-NO
R14, R17: 1Meg; 0603-NO
SENSE0, SENSE1, SENSE3: JST PH 3; JSTPH3
SJ1: SOLDERJUMPERCLOSED; SOLDERJUMPER_CLOSEDWIRE
SJ2: SOLDERJUMPER_2WAY; SOLDERJUMPER_2WAY_OPEN_NOPASTE
SP1: SPEAKER_7.5MM; BUZZER_SMT_7.5MM
SW2, SW5, SW6, SW7: FSM2JMTR; TACTILE_3X6MM
SW3: EG1390
SW4: SPST_TACT-KMR2; KMR2
TFT1: DISP_TFT_1.54IN_240X240_22P; TFT_1.54IN_240X240_22PIN
TP1, TP2, TP3, TP6: TESTPOINTROUND1.5MMNO; TESTPOINT_ROUND_1.5MM_NO
TP4, TP5, TP7, TP8: SEWTAP_SMTNUTM3; SMT_NUT_3MM
U1: DPS3; BMX280_COMBO
U2: ALS-PT19; ALS-PT19-315C
U3: ESP32-S2-MODULE_WROVER; MODULE_ESP32-S2-WROVER
U4: AP2112K-3.3; SOT23-5
U5: AHT20; SNR6-1.0-3X3X1MM
X1: CAPTOUCH_MONOPAD_6X9; CAPTOUCH_6X9MM
X3, X5: CAPTOUCH_MONOPAD_7X9; CAPTOUCH_7X9MM
X4: USB C; USB_C_CUSB31-CFM2AX-01-X
X6: CAPTOUCH_5SLIDER_10MM; CAPTOUCH_5SLIDER

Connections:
3.3V: C2.1, C3.1, C4.1, C5.1, C7.1, C9.2, C10.1, C12.1, C13.1, C17.1, CONN1.2 (V+), DS0.3 (VDD), DS1.3 (VDD), DS2.3 (VDD), DS3.3 (VDD), DS4.3 (VDD), JP1.1, JP1.2, JP2.1, JP2.2, JP2.T1 (1), JP2.T2 (2), R1.2, R4.1, R5.1, R7.1, SJ1.2, SJ2.3, SW2.P$1, SW5.P$1, SW6.P$1, TFT1.1 (LEDA), TFT1.3 (IM2), TFT1.4 (IM1), TFT1.6 (VCI), U1.2 (CSB), U1.5 (SDO), U1.6 (VDDIO), U1.8 (VDD), U2.C, U3.2 (3V3), U4.5 (OUT), U5.2 (VDD)
A0_JST: R18.1, SENSE1.3
A2_JST2: R2.1, SENSE3.3
AD0: D6.C, R18.2, U3.20 (IO17/DAC1)
AD1: D1.C, R16.2, U3.5 (IO2)
AD1_JST: R16.1, SENSE0.3
AD2: D2.C, R2.2, U3.4 (IO1)
BOOT0: SW4.2 (S), SW4.4 (S1), TP1.P$1, U3.3 (IO0_BOOT0)
BUTTON_DOWN: SW6.P$2, U3.6 (IO3)
BUTTON_SEL: SW5.P$2, U3.7 (IO4)
BUTTON_UP: SW2.P$2, U3.8 (IO5)
CC1: R8.2, X4.A5 (CC1)
CC2: R3.2, X4.B5 (CC2)
CT6: U3.9 (IO6), X1.P$1
CT7: U3.10 (IO7), X3.P$1
CT8: U3.11 (IO8), X5.P$1
CT9: U3.12 (IO9), X6.P$5 (4)
CT10: U3.13 (IO10), X6.P$4 (3)
CT11: U3.14 (IO11), X6.P$3 (2)
CT12: U3.15 (IO12), X6.P$2 (1)
CT13: U3.16 (IO13), X6.P$1 (0)
D+: U3.23 (IO20/D+), X4.A6 (D+), X4.B6 (D+)
D-: U3.22 (IO19/D-), X4.A7 (D-), X4.B7 (D-)
DS_CLK: DS0.5 (CKI), U3.18 (IO15)
DS_DATA: DS0.6 (DI), U3.17 (IO14)
EN: Q3.1 (G), R12.2, SW3.P2
GND: C1.2, C2.2, C3.2, C4.2, C5.2, C6.2, C7.2, C9.1, C10.2, C11.2, C12.2, C13.2, C14.2, C15.2, C17.2, C20.2, CONN1.1 (GND), CONN1.MT1 (MT), CONN1.MT2 (MT), D1.A, D2.A, D6.A, DS0.4 (GND), DS1.4 (GND), DS2.4 (GND), DS3.4 (GND), DS4.4 (GND), JP1.5, JP1.6, JP2.5, JP2.6, JP2.T5 (5), JP2.T6 (6), L0.C, ON0.C, Q1.2 (S), Q4.2 (S), R3.1, R8.1, R10.1, R13.1, R14.1, R17.1, R20.1, SENSE0.1, SENSE0.NC1 (MT), SENSE0.NC2 (MT), SENSE1.1, SENSE1.NC1 (MT), SENSE1.NC2 (MT), SENSE3.1, SENSE3.NC1 (MT), SENSE3.NC2 (MT), SW3.O1, SW3.O2, SW3.P1, SW3.S1, SW4.1, SW4.3 (P1), SW7.P$1, TFT1.5 (IM0), TFT1.7 (DB7), TFT1.8 (DB6), TFT1.9 (DB5), TFT1.10 (DB4), TFT1.11 (DB3), TFT1.12 (DB2), TFT1.13 (DB1), TFT1.14 (DB0), TFT1.15 (~RD), TFT1.22 (GND), TFT1.SUPPORT1 (GND), TFT1.SUPPORT2 (GND), U1.1 (GND), U1.7 (GND), U3.1 (GND), U3.26 (GND), U3.42 (GND), U3.43_1 (EXP), U3.43_2 (EXP)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
IO38_DOUBLETAP: C6.1, R17.2, U3.32 (IO38)
LIGHT: R20.2, U2.E, U3.21 (IO18/DAC2)
MISO: R9.2, U3.31 (IO37)
MOSI: TFT1.21 (SDA), U3.29 (IO35)
unnamed: L0.A, R9.1
unnamed: R6.2, SJ1.1
unnamed: ON0.A, R6.1
unnamed: D3.A, Q4.3 (D), SP1.-
unnamed: DS0.1 (DO), DS1.6 (DI)
unnamed: DS0.2 (CKO), DS1.5 (CKI)
unnamed: DS1.1 (DO), DS2.6 (DI)
unnamed: DS1.2 (CKO), DS2.5 (CKI)
unnamed: DS2.1 (DO), DS3.6 (DI)
unnamed: DS2.2 (CKO), DS3.5 (CKI)
unnamed: DS3.1 (DO), DS4.6 (DI)
unnamed: DS3.2 (CKO), DS4.5 (CKI)
unnamed: Q1.3 (D), R11.1
PIR_SENSE: JP1.3, JP1.4, JP2.3, JP2.4, JP2.T3 (3), JP2.T4 (4), R14.2, U3.19 (IO16)
RESET: C14.1, R1.1, SW7.P$2, TP6.P$1, U3.41 (EN)
RXD0: TP2.P$1, U3.38 (RXD0)
SCK: TFT1.17 (RS/CLK), U3.30 (IO36)
SCL: CONN1.4 (SCL), R5.2, U1.4 (SCK), U3.27 (IO33), U5.3 (SCL)
SDA: CONN1.3 (SDA), R7.2, U1.3 (SDI), U3.28 (IO34), U5.4 (SDA)
SPKR: Q4.1 (G), R13.2, U3.36 (IO42/TMS)
TFT_CS: R4.2, TFT1.18 (~CS), U3.34 (IO40/TDO)
TFT_DC: TFT1.16 (~WR/D~C), U3.33 (IO39/TCK)
TFT_LEDK: R11.2, TFT1.2 (LEDK)
TFT_LITE: Q1.1 (G), R10.2, U3.24 (IO21)
TFT_RESET: TFT1.20 (RESET), U3.35 (IO41/TDI)
TXD0: TP3.P$1, U3.37 (TXD0)
VBUS: C1.1, C15.1, Q3.2 (S), R12.1, X4.A4B9 (VBUS), X4.B4A9 (VBUS)
VCC: C20.1, SENSE0.2, SENSE1.2, SENSE3.2, SJ2.2
VHIGH: C11.1, D3.C, Q3.3 (D), SJ2.1, SP1.+, U4.1 (IN), U4.3 (EN)

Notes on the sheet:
Stemma QT
3.3V Regulator
USB Type C
Dropout Voltage (25°C): 100mA: ~250/~40mV 300mA: ~300/~125mV 600mA: ~375/~260mV
PSRAMCS
Limor Fried
TFT Display
CapTouch
ESP32-S2 WROVER
JST / STEMMA Connectors
~10uA
Baro / Temp / Hum
Red LED
Power LED
DotStar LEDs
Switches
Light / Motion
Boot/Reset

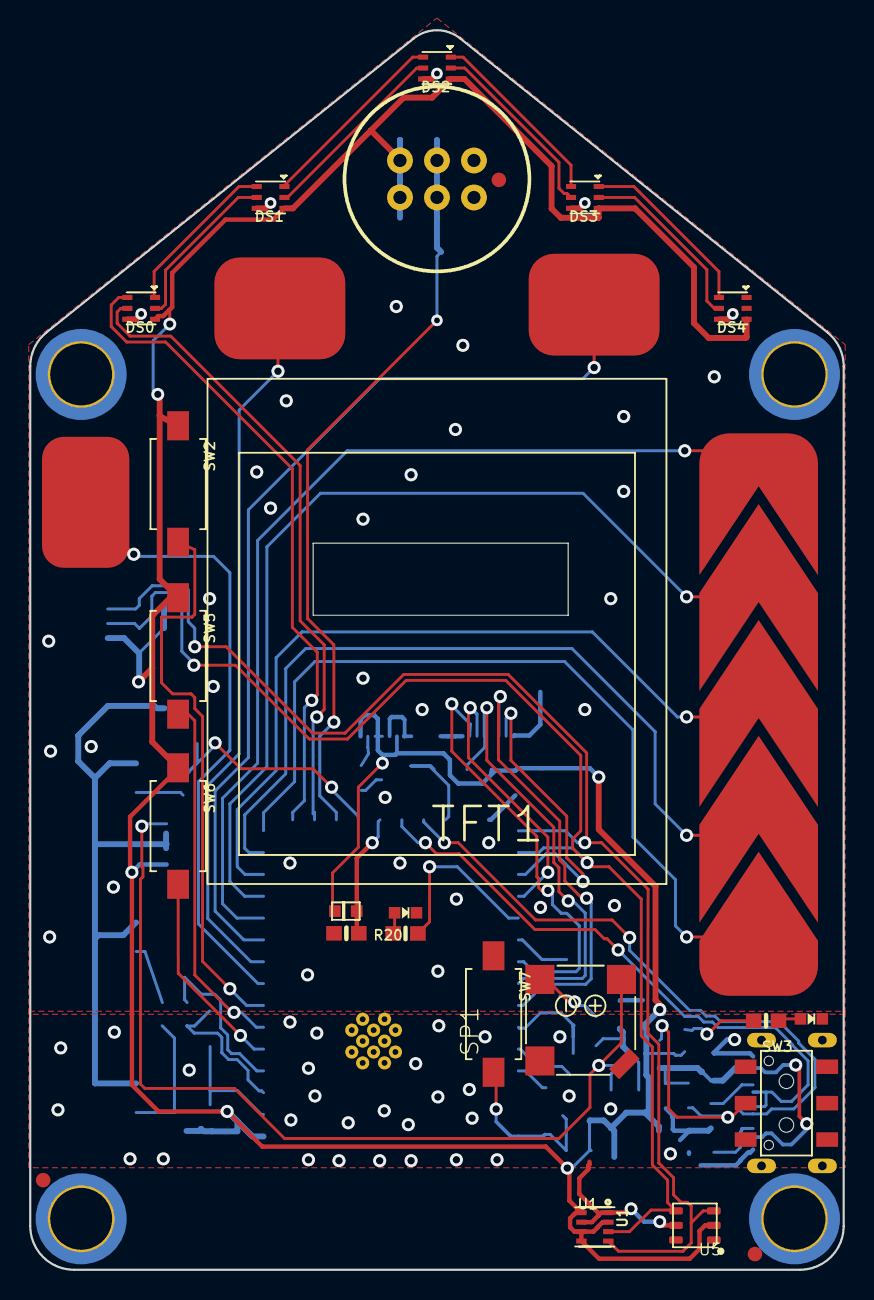
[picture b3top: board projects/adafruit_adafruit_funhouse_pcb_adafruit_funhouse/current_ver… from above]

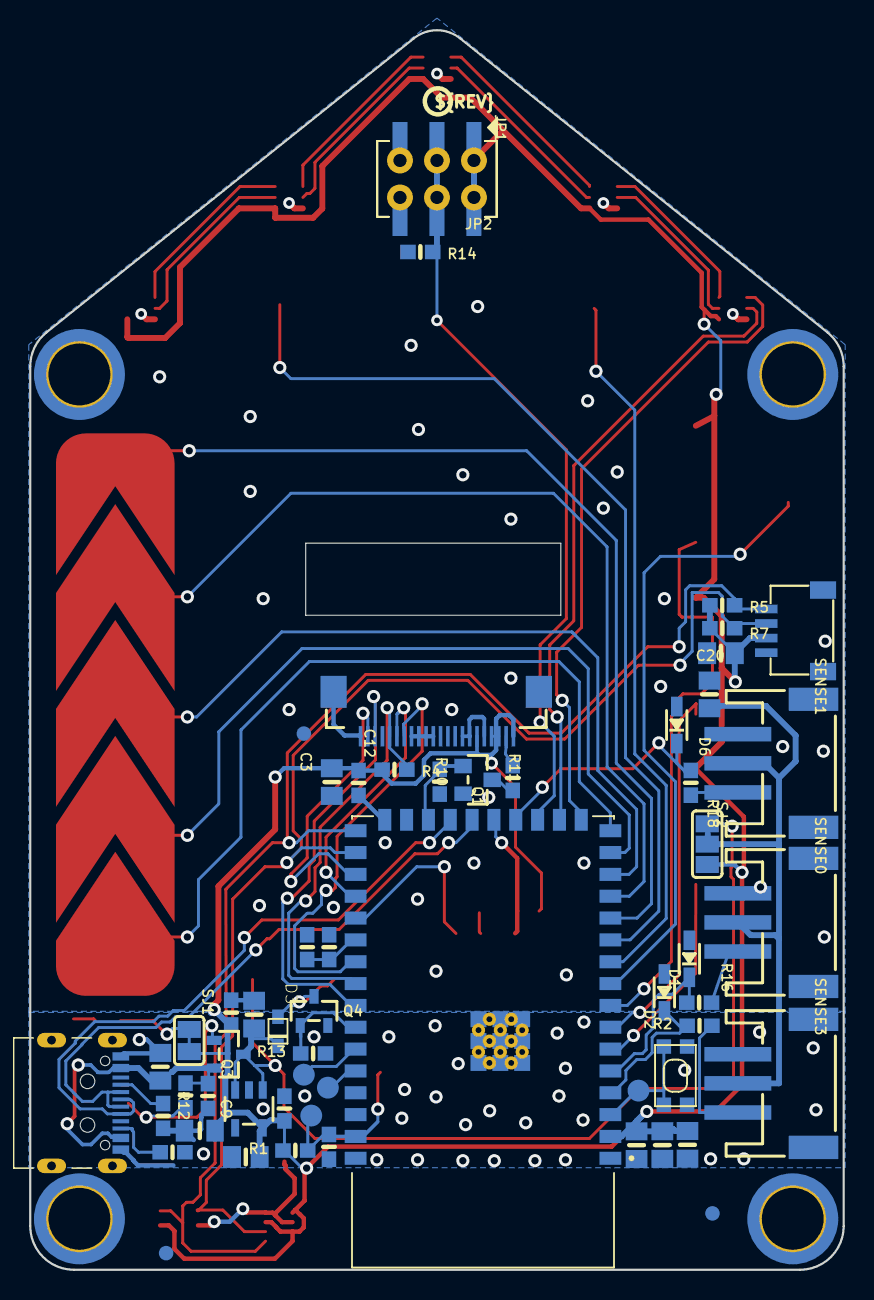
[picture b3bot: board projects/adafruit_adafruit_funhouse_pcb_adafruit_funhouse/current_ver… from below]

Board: 2 copper layers, 55.9 x 85.1 mm, 91 parts (63 on the bottom side), 60 nets.

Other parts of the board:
U$41: PCBFEAT-REV-040
U$45: FUNHOUSE_FRONT
U$69: FUNHOUSE_BACK

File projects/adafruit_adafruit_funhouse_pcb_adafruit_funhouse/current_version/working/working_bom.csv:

"Id";"Designator";"Footprint";"Quantity";"Designation";"Supplier and ref";
1;"R9,R20,R5,R1,R13,R10,R7,R4,R12";"0603-NO";9;"10K";;;
2;"X1";"CAPTOUCH_6X9MM";1;"CAPTOUCH_10MM";;;
3;"U5";"SNR6-1.0-3X3X1MM";1;"AHT20";;;
4;"X6";"CAPTOUCH_5SLIDER";1;"CAPTOUCH_5SLIDER_10MM";;;
5;"SW5,SW2,SW6,SW7";"TACTILE_3X6MM";4;"FSM2JMTR";;;
6;"TFT1";"TFT_1.54IN_240X240_22PIN";1;"DISP_TFT_1.54IN_240X240_22P";;;
7;"U$45";"FUNHOUSE_FRONT";1;"";;;
8;"ON0";"CHIPLED_0603_NOOUTLINE";1;"GREEN";;;
9;"DS4,DS1,DS3,DS2,DS0";"APA102_2020";5;"APA102-2020";;;
10;"FID2,FID1,FID3,FID4,FID5,FID6";"FIDUCIAL_1MM";6;"FIDUCIAL_1MM";;;
11;"U1";"BMX280_COMBO";1;"DPS3";;;
12;"U2";"ALS-PT19-315C";1;"ALS-PT19";;;
13;"L0";"CHIPLED_0603_NOOUTLINE";1;"RED";;;
14;"X3,X5";"CAPTOUCH_7X9MM";2;"CAPTOUCH_10MM";;;
15;"SP1";"BUZZER_SMT_7.5MM";1;"7.5mm SPK";;;
16;"R6";"0603-NO";1;"47K";;;
17;"SW3";"EG1390";1;"EG1390";;;
18;"C12,C14,C6";"0603-NO";3;"1uF";;;
19;"C3,C10,C7,C4,C13,C11,C17";"0805-NO";7;"10µF";;;
20;"TP8,TP7,TP5,TP4";"SMT_NUT_3MM";4;"SEWTAP_SMTNUTM3";;;
21;"SW4";"KMR2";1;"SPST_TACT-KMR2";;;
22;"D6,D1,D2";"SOD-323";3;"3.6V";;;
23;"R18,R16,R2";"0603-NO";3;"1K";;;
24;"Q3";"SOT23-R";1;"DMG3415U-7";;;
25;"SJ2";"SOLDERJUMPER_2WAY_OPEN_NOPASTE";1;"";;;
26;"TP2,TP6,TP3,TP1";"TESTPOINT_ROUND_1.5MM_NO";4;"";;;
27;"CONN1";"JST_SH4";1;"STEMMA_I2C_QT";;;
28;"C2,C15,C5";"0603-NO";3;"0.1uF";;;
29;"C20,C1";"0805-NO";2;"10uF";;;
30;"Q1";"SOT23-WIDE";1;"BSS138";;;
31;"SENSE1,SENSE3,SENSE0";"JSTPH3";3;"JST PH 3";;;
32;"R11";"0603-NO";1;"100";;;
33;"SJ1";"SOLDERJUMPER_CLOSEDWIRE";1;"";;;
34;"C9";"0805_10MGAP";1;"10uF/10V+";;;
35;"R14,R17";"0603-NO";2;"1Meg";;;
36;"R3,R8";"0603-NO";2;"5.1K";;;
37;"X4";"USB_C_CUSB31-CFM2AX-01-X";1;"USB C";;;
38;"U$41";"PCBFEAT-REV-040";1;"";;;
39;"JP2";"2X03_SMTTHM";1;"";;;
40;"U4";"SOT23-5";1;"AP2112K-3.3";;;
41;"D3";"SOD-323F";1;"1N4148";;;
42;"Q4";"SOT23-R";1;"BSS138";;;
43;"JP1";"2X03_SMT_4UCON_14113";1;"2x3 SMT";;;
44;"U3";"MODULE_ESP32-S2-WROVER";1;"ESP32-S2-MODULE_WROVER";;;
45;"U$69";"FUNHOUSE_BACK";1;"";;;
